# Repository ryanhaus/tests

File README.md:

# sandbox
Sandbox area for small tests and projects that don't constitute a full repo

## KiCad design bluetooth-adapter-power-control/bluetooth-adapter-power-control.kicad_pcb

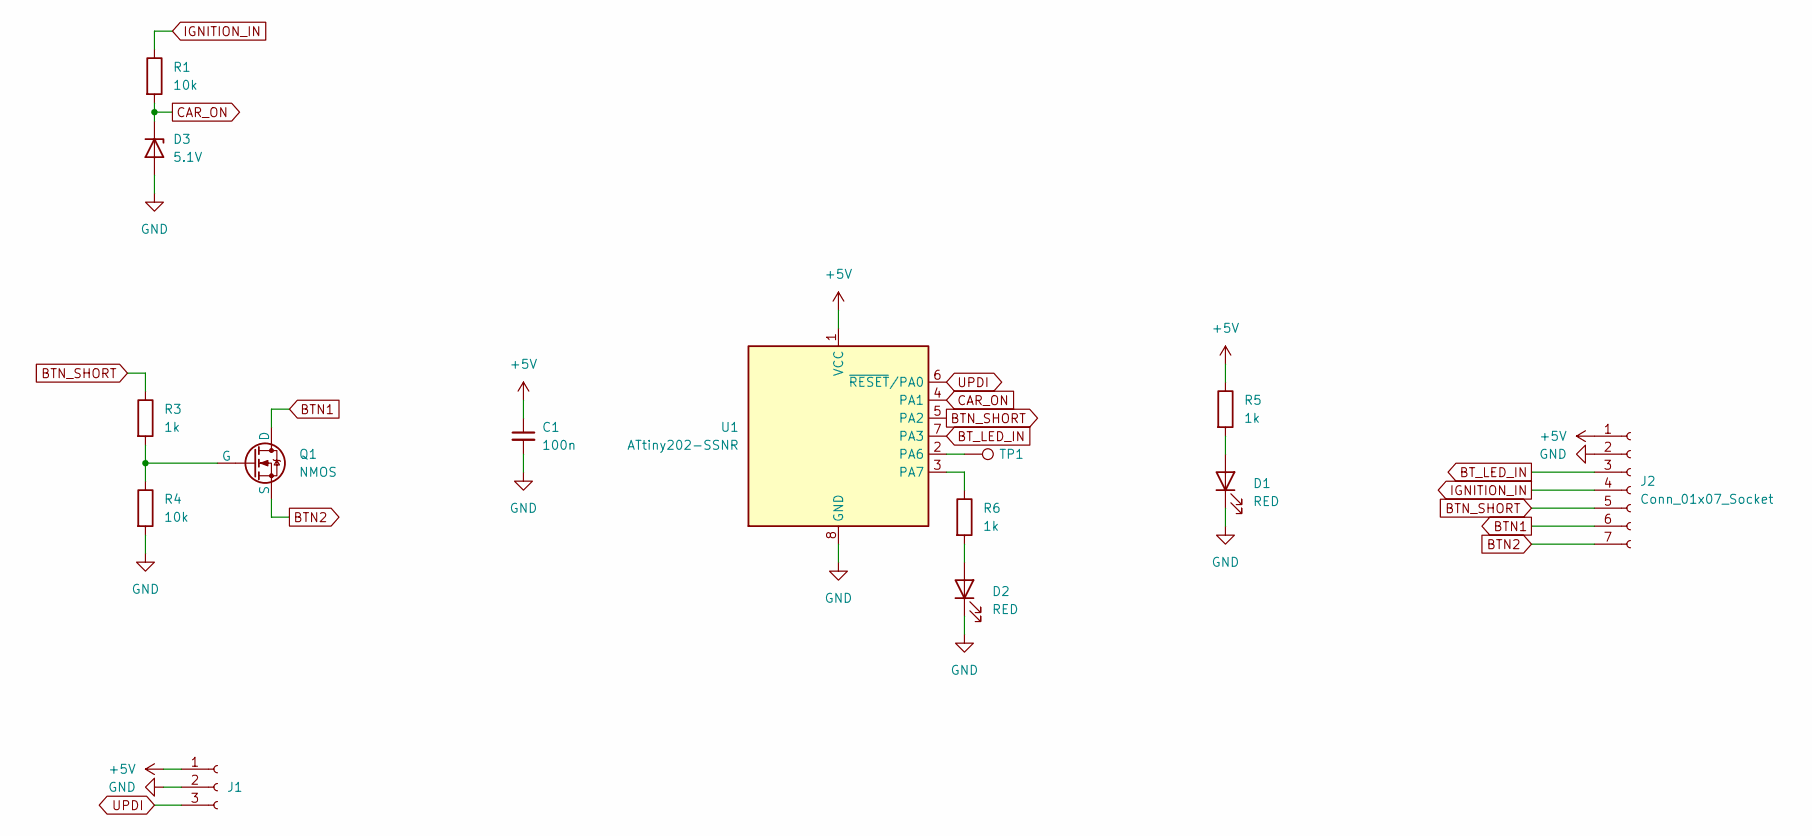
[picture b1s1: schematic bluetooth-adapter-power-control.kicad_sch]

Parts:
C1: 100n; C_0603_1608Metric
D1, D2: RED; LED_0603_1608Metric
D3: 5.1V; D_SOD-523
J1: UPDI; PinHeader_1x03_P1.27mm_Vertical
J2: Conn_01x07_Socket; PinHeader_1x07_P1.27mm_Vertical
Q1: NMOS; SOT-23
R1, R4: 10k; R_0603_1608Metric
R3, R5, R6: 1k; R_0603_1608Metric
TP1: TestPoint; TestPoint_Pad_D1.0mm
U1: ATtiny202-SSNR; SOIC-8_3.9x4.9mm_P1.27mm

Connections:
+5V: C1.1, J1.1, J2.1, R5.1, U1.1 (VCC)
BTN1: J2.6, Q1.1 (D)
BTN2: J2.7, Q1.3 (S)
BTN_SHORT: J2.5, R3.1, U1.5 (PA2)
BT_LED_IN: J2.3, U1.7 (PA3)
CAR_ON: D3.1 (K), R1.2, U1.4 (PA1)
GND: C1.2, D1.1 (K), D2.1 (K), D3.2 (A), J1.2, J2.2, R4.2, U1.8 (GND)
IGNITION_IN: J2.4, R1.1
unnamed: D1.2 (A), R5.2
unnamed: D2.2 (A), R6.2
unnamed: Q1.2 (G), R3.2, R4.1
unnamed: TP1.1, U1.2 (PA6)
unnamed: R6.1, U1.3 (PA7)
UPDI: J1.3, U1.6 (~RESET/PA0)

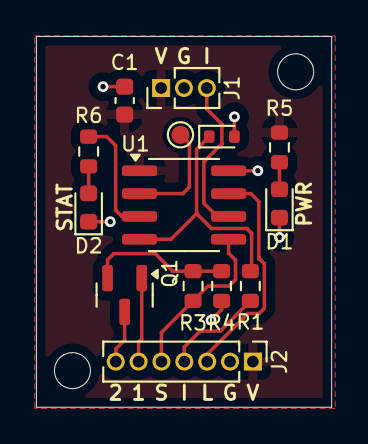
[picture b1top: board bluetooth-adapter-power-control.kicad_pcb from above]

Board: 2 copper layers, 16.4 x 20.6 mm, 14 parts (0 on the bottom side), 14 nets.

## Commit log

2025-06-14 Create rust-c-interoperability
2025-06-14 Ignore Rust build dirs
2025-06-14 rust-c-interopability: add simple test C function
2025-06-14 rust-c-interopability: add Rust bindings for simple C function
2025-06-14 rust-c-interopability: add build.rs script to build C file w/ cc dependency
2025-06-14 rust-c-interopability: add stdint.h header to C file
2025-06-14 rust-c-interopability: call C function from Rust
2025-06-15 rust-framebuffer: create project
2025-06-15 rust-framebuffer: get simple framebuffer test working
2025-06-15 rust-framebuffer: test out differing window/buffer sizes
2025-06-15 rust-framebuffer: change scale & display test
2025-06-22 Create bluetooth-adapter-power-control project
2025-06-22 Update gitignore
2025-06-22 bluetooth-adapter-power-control: Upgrade files from 6.0 to 9.0
2025-06-22 Add backups and lck files to gitignore
2025-06-24 bluetooth-adapter-power-control: Finish schematic
2025-06-24 bluetooth-adapter-power-control: add footprints
2025-06-24 bluetooth-adapter-power-control: Fix schematic & footprints, update PCB
2025-06-24 Ignore KiCAD auto-saves
2025-06-24 bluetooth-adapter-power-control: change 5 pin header to 7 to include button short pins
2025-06-24 bluetooth-adapter-power-control: initial PCB layout (no routing)
2025-06-24 bluetooth-adapter-power-control: Finish PCB routing
2025-06-24 bluetooth-adapter-power-control: Change ignition voltage resistor divider to use a zener diode
2025-06-24 bluetooth-adapter-power-control: Switch UPDI header to have GND in the middle
2025-06-24 bluetooth-adapter-power-control: Add pin labels and 1mm mounting holes
2025-06-24 bluetooth-adapter-power-control: add more text to PCB
2025-06-24 fan-board-interface: Create folder & add main.py progress
2025-06-24 fan-board-interface: add shebang for main.py
2025-06-24 Add README
2025-06-24 fan-board-interface: change 'len' parameter to 'n' to prevent confusion with the len method
2025-06-24 fan-board-interface: finish EEPROM methods
2025-06-24 fan-board-interface: convert to all spaces
2025-06-25 fan-board-interface: update main.py to use LED controller, EEPROM, fan controller; updates from 6-25-25
2025-06-26 fan-board-interface: make i2c_read always return an array
2025-06-26 fan-board-interface: fix issue that causes 64th byte of page to not be written
2025-06-26 fan-board-interface: verify EEPROM page writes
2025-06-26 fan-board-interface: read power-on-seconds
2025-06-26 fan-board-interface: have the two fans at different PWMs
2025-06-26 fan-board-interface: stop reading and displaying VOUT twice
2025-06-26 fan-board-interface: split everything to separate files
2025-06-26 fan-board-interface: fix missing util import in smbus
2025-06-26 fan-board-interface: comments & formatting
2025-06-26 fan-board-interface: add missing 'n_bytes' parameter when writing to LED controller
2025-06-30 fan-board-interface: add simple CLI tool
2025-06-30 updi-py: add to repo
2025-06-30 Change repo name to 'sandbox' (from 'tests')
2025-06-30 Completely abstract I2C methods by abstracting flags to not be specific to Aardvark
2025-07-01 fan-board-interface: add missing return statement
2025-07-01 vivado-pullup-test: add to repo
2025-07-01 vivado-pullup-test: fix to drive output either high-impedance or as 0
2025-07-02 updi-phy-test: add to repo w/ updi-fpga submodule
2025-07-02 updi-phy-test: add constraints & top-level module
2025-07-02 updi-phy-test: send bytes from 0x00-0xFF repeatedly
2025-07-02 updi-phy-test: update updi-fpga submodule & configure to use fifo's 'almost_full' instead of 'full'
